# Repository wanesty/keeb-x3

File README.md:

# The RP2040 chip-powered V2 of this project has been relocated to [Codeberg](https://codeberg.org/Wanesty/keeb-x3)
it's developement will remain there for present and future iterations if I ultimately favor it over GitHub.

---

# keeb-x3
a 1800-style ortholinear keyboard with 105 keys

- this is my attempt as a contenporain keyboard, ditching the legacy staggered layout for ortho, which to me makes way more sense since we don't have to deal with typewriter hammers anymore.
- it is also made to be easily swapped between QWERTY, Dvorak and Colemak, to accentuate the need to detach ourselves from the 1873 typewriters.

#### The Pico's USB B have to be wired to the "keeb-x3"'s USB C port by using the "TP1, TP2, TP3" pads availlable on the bottom of the Pico

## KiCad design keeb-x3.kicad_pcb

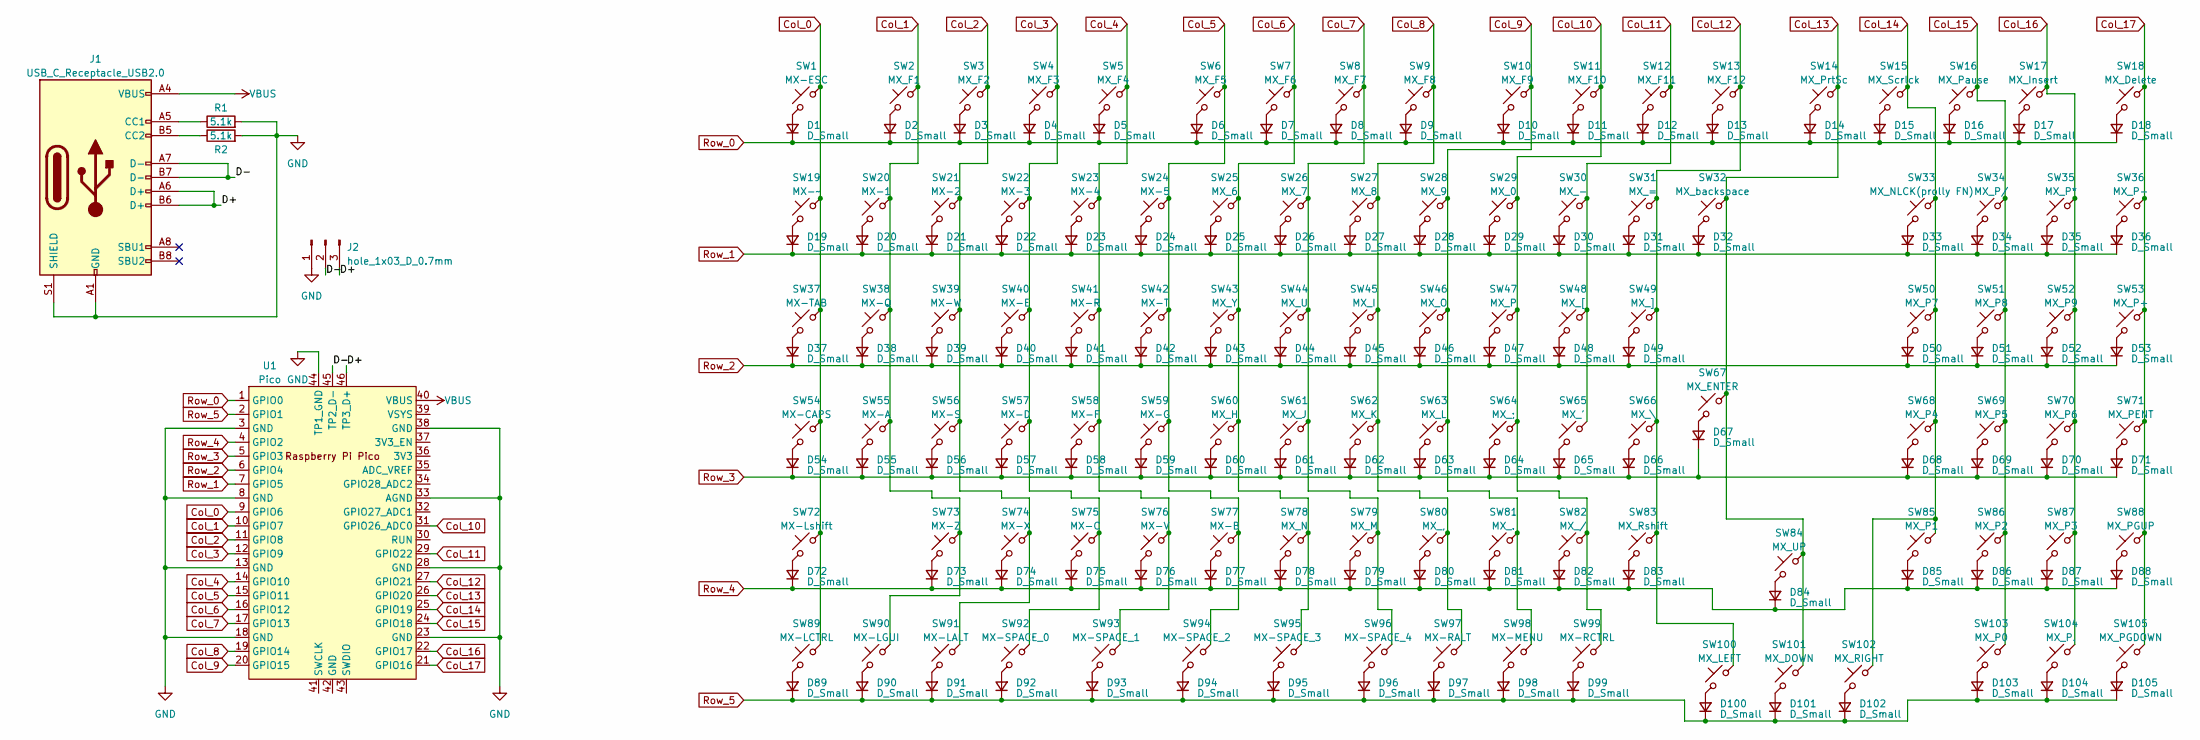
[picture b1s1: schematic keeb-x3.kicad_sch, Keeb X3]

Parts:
D1, D2, D3, D4, D5, D6, D7, D8, D9, D10, D11, D12, D13, D14, D15, D16, D17, D18, D19, D20, D21, D22, D23, D24, D25, D26, D27, D28, D29, D30, D31, D32, D33, D34, D35, D36, D37, D38, D39, D40, D41, D42, D43, D44, D45, D46, D47, D48, D49, D50, D51, D52, D53, D54, D55, D56, D57, D58, D59, D60, D61, D62, D63, D64, D65, D66, D67, D68, D69, D70, D71, D72, D73, D74, D75, D76, D77, D78, D79, D80, D81, D82, D83, D84, D85, D86, D87, D88, D89, D90, D91, D92, D93, D94, D95, D96, D97, D98, D99, D100, D101, D102, D103, D104, D105: D_Small; D_DO-35_SOD27_P7.62mm_Horizontal_ref_center
J1: USB_C_Receptacle_USB2.0; USB_C_Receptacle_GCT_USB4085
J2: hole_1x03_D_0.7mm
R1, R2: 5.1k; R_Axial_DIN0204_L3.6mm_D1.6mm_P7.62mm_Horizontal
SW1: MX-ESC; SW_Hotswap_Kailh_MX_plated_1.00u
SW2: MX_F1; SW_Hotswap_Kailh_MX_plated_1.00u
SW3: MX_F2; SW_Hotswap_Kailh_MX_plated_1.00u
SW4: MX_F3; SW_Hotswap_Kailh_MX_plated_1.00u
SW5: MX_F4; SW_Hotswap_Kailh_MX_plated_1.00u
SW6: MX_F5; SW_Hotswap_Kailh_MX_plated_1.00u
SW7: MX_F6; SW_Hotswap_Kailh_MX_plated_1.00u
SW8: MX_F7; SW_Hotswap_Kailh_MX_plated_1.00u
SW9: MX_F8; SW_Hotswap_Kailh_MX_plated_1.00u
SW10: MX_F9; SW_Hotswap_Kailh_MX_plated_1.00u
SW11: MX_F10; SW_Hotswap_Kailh_MX_plated_1.00u
SW12: MX_F11; SW_Hotswap_Kailh_MX_plated_1.00u
SW13: MX_F12; SW_Hotswap_Kailh_MX_plated_1.00u
SW14: MX_PrtSc; SW_Hotswap_Kailh_MX_plated_1.00u
SW15: MX_Scrlck; SW_Hotswap_Kailh_MX_plated_1.00u
SW16: MX_Pause; SW_Hotswap_Kailh_MX_plated_1.00u
SW17: MX_Insert; SW_Hotswap_Kailh_MX_plated_1.00u
SW18: MX_Delete; SW_Hotswap_Kailh_MX_plated_1.00u
SW19: MX-~; SW_Hotswap_Kailh_MX_plated_1.00u
SW20: MX-1; SW_Hotswap_Kailh_MX_plated_1.00u
SW21: MX-2; SW_Hotswap_Kailh_MX_plated_1.00u
SW22: MX-3; SW_Hotswap_Kailh_MX_plated_1.00u
SW23: MX-4; SW_Hotswap_Kailh_MX_plated_1.00u
SW24: MX-5; SW_Hotswap_Kailh_MX_plated_1.00u
SW25: MX_6; SW_Hotswap_Kailh_MX_plated_1.00u
SW26: MX_7; SW_Hotswap_Kailh_MX_plated_1.00u
SW27: MX_8; SW_Hotswap_Kailh_MX_plated_1.00u
SW28: MX_9; SW_Hotswap_Kailh_MX_plated_1.00u
SW29: MX_0; SW_Hotswap_Kailh_MX_plated_1.00u
SW30: MX_-; SW_Hotswap_Kailh_MX_plated_1.00u
SW31: MX_=; SW_Hotswap_Kailh_MX_plated_1.00u
SW32: MX_backspace; SW_Hotswap_Kailh_MX_plated_1.50u
SW33: MX_NLCK(prolly FN); SW_Hotswap_Kailh_MX_plated_1.00u
SW34: MX_P/; SW_Hotswap_Kailh_MX_plated_1.00u
SW35: MX_P*; SW_Hotswap_Kailh_MX_plated_1.00u
SW36: MX_P-; SW_Hotswap_Kailh_MX_plated_1.00u
SW37: MX-TAB; SW_Hotswap_Kailh_MX_plated_1.00u
SW38: MX-Q; SW_Hotswap_Kailh_MX_plated_1.00u
SW39: MX-W; SW_Hotswap_Kailh_MX_plated_1.00u
SW40: MX-E; SW_Hotswap_Kailh_MX_plated_1.00u
SW41: MX-R; SW_Hotswap_Kailh_MX_plated_1.00u
SW42: MX-T; SW_Hotswap_Kailh_MX_plated_1.00u
SW43: MX_Y; SW_Hotswap_Kailh_MX_plated_1.00u
SW44: MX_U; SW_Hotswap_Kailh_MX_plated_1.00u
SW45: MX_I; SW_Hotswap_Kailh_MX_plated_1.00u
SW46: MX_O; SW_Hotswap_Kailh_MX_plated_1.00u
SW47: MX_P; SW_Hotswap_Kailh_MX_plated_1.00u
SW48: MX_[; SW_Hotswap_Kailh_MX_plated_1.00u
SW49: MX_]; SW_Hotswap_Kailh_MX_plated_1.00u
SW50: MX_P7; SW_Hotswap_Kailh_MX_plated_1.00u
SW51: MX_P8; SW_Hotswap_Kailh_MX_plated_1.00u
SW52: MX_P9; SW_Hotswap_Kailh_MX_plated_1.00u
SW53: MX_P+; SW_Hotswap_Kailh_MX_plated_1.00u
SW54: MX-CAPS; SW_Hotswap_Kailh_MX_plated_1.00u
SW55: MX-A; SW_Hotswap_Kailh_MX_plated_1.00u
SW56: MX-S; SW_Hotswap_Kailh_MX_plated_1.00u
SW57: MX-D; SW_Hotswap_Kailh_MX_plated_1.00u
SW58: MX-F; SW_Hotswap_Kailh_MX_plated_1.00u
SW59: MX-G; SW_Hotswap_Kailh_MX_plated_1.00u
SW60: MX_H; SW_Hotswap_Kailh_MX_plated_1.00u
SW61: MX_J; SW_Hotswap_Kailh_MX_plated_1.00u
SW62: MX_K; SW_Hotswap_Kailh_MX_plated_1.00u
SW63: MX_L; SW_Hotswap_Kailh_MX_plated_1.00u
SW64: MX_;; SW_Hotswap_Kailh_MX_plated_1.00u
SW65: MX_'; SW_Hotswap_Kailh_MX_plated_1.00u
SW66: MX_\; SW_Hotswap_Kailh_MX_plated_1.00u
SW67: MX_ENTER; SW_Hotswap_Kailh_MX_plated_ISOEnter_180deg
SW68: MX_P4; SW_Hotswap_Kailh_MX_plated_1.00u
SW69: MX_P5; SW_Hotswap_Kailh_MX_plated_1.00u
SW70: MX_P6; SW_Hotswap_Kailh_MX_plated_1.00u
SW71: MX_PENT; SW_Hotswap_Kailh_MX_plated_1.00u
SW72: MX-Lshift; SW_Hotswap_Kailh_MX_plated_2.00u
SW73: MX-Z; SW_Hotswap_Kailh_MX_plated_1.00u
SW74: MX-X; SW_Hotswap_Kailh_MX_plated_1.00u
SW75: MX-C; SW_Hotswap_Kailh_MX_plated_1.00u
SW76: MX-V; SW_Hotswap_Kailh_MX_plated_1.00u
SW77: MX-B; SW_Hotswap_Kailh_MX_plated_1.00u
SW78: MX_N; SW_Hotswap_Kailh_MX_plated_1.00u
SW79: MX_M; SW_Hotswap_Kailh_MX_plated_1.00u
SW80: MX_,; SW_Hotswap_Kailh_MX_plated_1.00u
SW81: MX_.; SW_Hotswap_Kailh_MX_plated_1.00u
SW82: MX_/; SW_Hotswap_Kailh_MX_plated_1.00u
SW83: MX_Rshift; SW_Hotswap_Kailh_MX_plated_2.00u
SW84: MX_UP; SW_Hotswap_Kailh_MX_plated_1.00u
SW85: MX_P1; SW_Hotswap_Kailh_MX_plated_1.00u
SW86: MX_P2; SW_Hotswap_Kailh_MX_plated_1.00u
SW87: MX_P3; SW_Hotswap_Kailh_MX_plated_1.00u
SW88: MX_PGUP; SW_Hotswap_Kailh_MX_plated_1.00u
SW89: MX-LCTRL; SW_Hotswap_Kailh_MX_plated_1.00u
SW90: MX-LGUI; SW_Hotswap_Kailh_MX_plated_1.00u
SW91: MX-LALT; SW_Hotswap_Kailh_MX_plated_1.00u
SW92: MX-SPACE_0; SW_Hotswap_Kailh_MX_plated_1.00u
SW93: MX-SPACE_1; SW_Hotswap_Kailh_MX_plated_2.00u
SW94: MX-SPACE_2; SW_Hotswap_Kailh_MX_plated_1.00u
SW95: MX-SPACE_3; SW_Hotswap_Kailh_MX_plated_2.00u
SW96: MX-SPACE_4; SW_Hotswap_Kailh_MX_plated_1.00u
SW97: MX-RALT; SW_Hotswap_Kailh_MX_plated_1.00u
SW98: MX-MENU; SW_Hotswap_Kailh_MX_plated_1.00u
SW99: MX-RCTRL; SW_Hotswap_Kailh_MX_plated_1.00u
SW100: MX_LEFT; SW_Hotswap_Kailh_MX_plated_1.00u
SW101: MX_DOWN; SW_Hotswap_Kailh_MX_plated_1.00u
SW102: MX_RIGHT; SW_Hotswap_Kailh_MX_plated_1.00u
SW103: MX_P0; SW_Hotswap_Kailh_MX_plated_1.00u
SW104: MX_P.; SW_Hotswap_Kailh_MX_plated_1.00u
SW105: MX_PGDOWN; SW_Hotswap_Kailh_MX_plated_1.00u
U1: Pico; RPi_Pico_SMD_TH

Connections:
/D+: J1.A6 (D+), J1.B6 (D+), J2.3, U1.46 (TP3_D+)
/D-: J1.A7 (D-), J1.B7 (D-), J2.2, U1.45 (TP2_D-)
Col_0: SW1.1, SW19.1, SW37.1, SW54.1, SW72.1, SW89.1, U1.9 (GPIO6)
Col_1: SW2.1, SW20.1, SW38.1, SW55.1, SW73.1, SW90.1, U1.10 (GPIO7)
Col_2: SW3.1, SW21.1, SW39.1, SW56.1, SW74.1, SW91.1, U1.11 (GPIO8)
Col_3: SW4.1, SW22.1, SW40.1, SW57.1, SW75.1, SW92.1, U1.12 (GPIO9)
Col_4: SW5.1, SW23.1, SW41.1, SW58.1, SW76.1, SW93.1, U1.14 (GPIO10)
Col_5: SW6.1, SW24.1, SW42.1, SW59.1, SW77.1, SW94.1, U1.15 (GPIO11)
Col_6: SW7.1, SW25.1, SW43.1, SW60.1, SW78.1, SW95.1, U1.16 (GPIO12)
Col_7: SW8.1, SW26.1, SW44.1, SW61.1, SW79.1, SW96.1, U1.17 (GPIO13)
Col_8: SW9.1, SW27.1, SW45.1, SW62.1, SW80.1, SW97.1, U1.19 (GPIO14)
Col_9: SW10.1, SW28.1, SW46.1, SW63.1, SW81.1, SW98.1, U1.20 (GPIO15)
Col_10: SW11.1, SW29.1, SW47.1, SW64.1, SW82.1, SW99.1, U1.31 (GPIO26_ADC0)
Col_11: SW12.1, SW30.1, SW48.1, SW65.1, U1.29 (GPIO22)
Col_12: SW13.1, SW31.1, SW49.1, SW66.1, SW83.1, SW100.1, U1.27 (GPIO21)
Col_13: SW14.1, SW32.1, SW67.1, SW84.1, SW101.1, U1.26 (GPIO20)
Col_14: SW15.1, SW33.1, SW50.1, SW68.1, SW85.1, SW102.1, U1.25 (GPIO19)
Col_15: SW16.1, SW34.1, SW51.1, SW69.1, SW86.1, SW103.1, U1.24 (GPIO18)
Col_16: SW17.1, SW35.1, SW52.1, SW70.1, SW87.1, SW104.1, U1.22 (GPIO17)
Col_17: SW18.1, SW36.1, SW53.1, SW71.1, SW88.1, SW105.1, U1.21 (GPIO16)
GND: J1.A1 (GND), J1.A12 (GND), J1.B1 (GND), J1.B12 (GND), J1.S1 (SHIELD), J2.1, R1.2, R2.2, U1.3 (GND), U1.8 (GND), U1.13 (GND), U1.18 (GND), U1.23 (GND), U1.28 (GND), U1.33 (AGND), U1.38 (GND), U1.44 (TP1_GND)
unnamed: D1.2 (A), SW1.2
unnamed: D2.2 (A), SW2.2
unnamed: D3.2 (A), SW3.2
unnamed: D4.2 (A), SW4.2
unnamed: D5.2 (A), SW5.2
unnamed: D6.2 (A), SW6.2
unnamed: D7.2 (A), SW7.2
unnamed: D8.2 (A), SW8.2
unnamed: D9.2 (A), SW9.2
unnamed: D10.2 (A), SW10.2
unnamed: D11.2 (A), SW11.2
unnamed: D12.2 (A), SW12.2
unnamed: D13.2 (A), SW13.2
unnamed: D14.2 (A), SW14.2
unnamed: D15.2 (A), SW15.2
unnamed: D16.2 (A), SW16.2
unnamed: D17.2 (A), SW17.2
unnamed: D18.2 (A), SW18.2
unnamed: D19.2 (A), SW19.2
unnamed: D20.2 (A), SW20.2
unnamed: D21.2 (A), SW21.2
unnamed: D22.2 (A), SW22.2
unnamed: D23.2 (A), SW23.2
unnamed: D24.2 (A), SW24.2
unnamed: D25.2 (A), SW25.2
unnamed: D26.2 (A), SW26.2
unnamed: D27.2 (A), SW27.2
unnamed: D28.2 (A), SW28.2
unnamed: D29.2 (A), SW29.2
unnamed: D30.2 (A), SW30.2
unnamed: D31.2 (A), SW31.2
unnamed: D32.2 (A), SW32.2
unnamed: D33.2 (A), SW33.2
unnamed: D34.2 (A), SW34.2
unnamed: D35.2 (A), SW35.2
unnamed: D36.2 (A), SW36.2
unnamed: D37.2 (A), SW37.2
unnamed: D38.2 (A), SW38.2
unnamed: D39.2 (A), SW39.2
unnamed: D40.2 (A), SW40.2
unnamed: D41.2 (A), SW41.2
unnamed: D42.2 (A), SW42.2
unnamed: D43.2 (A), SW43.2
unnamed: D44.2 (A), SW44.2
unnamed: D45.2 (A), SW45.2
unnamed: D46.2 (A), SW46.2
unnamed: D47.2 (A), SW47.2
unnamed: D48.2 (A), SW48.2
unnamed: D49.2 (A), SW49.2
unnamed: D50.2 (A), SW50.2
unnamed: D51.2 (A), SW51.2
unnamed: D52.2 (A), SW52.2
unnamed: D53.2 (A), SW53.2
unnamed: D54.2 (A), SW54.2
unnamed: D55.2 (A), SW55.2
unnamed: D56.2 (A), SW56.2
unnamed: D57.2 (A), SW57.2
unnamed: D58.2 (A), SW58.2
unnamed: D59.2 (A), SW59.2
unnamed: D60.2 (A), SW60.2
unnamed: D61.2 (A), SW61.2
unnamed: D62.2 (A), SW62.2
unnamed: D63.2 (A), SW63.2
unnamed: D64.2 (A), SW64.2
unnamed: D65.2 (A), SW65.2
unnamed: D66.2 (A), SW66.2
unnamed: D67.2 (A), SW67.2
unnamed: D68.2 (A), SW68.2
unnamed: D69.2 (A), SW69.2
unnamed: D70.2 (A), SW70.2
unnamed: D71.2 (A), SW71.2
unnamed: D72.2 (A), SW72.2
unnamed: D73.2 (A), SW73.2
unnamed: D74.2 (A), SW74.2
unnamed: D75.2 (A), SW75.2
unnamed: D76.2 (A), SW76.2
unnamed: D77.2 (A), SW77.2
unnamed: D78.2 (A), SW78.2
unnamed: D79.2 (A), SW79.2
unnamed: D80.2 (A), SW80.2
unnamed: D81.2 (A), SW81.2
unnamed: D82.2 (A), SW82.2
unnamed: D83.2 (A), SW83.2
unnamed: D84.2 (A), SW84.2
unnamed: D85.2 (A), SW85.2
unnamed: D86.2 (A), SW86.2
unnamed: D87.2 (A), SW87.2
unnamed: D88.2 (A), SW88.2
unnamed: D89.2 (A), SW89.2
unnamed: D90.2 (A), SW90.2
unnamed: D91.2 (A), SW91.2
unnamed: D92.2 (A), SW92.2
unnamed: D93.2 (A), SW93.2
unnamed: D94.2 (A), SW94.2
unnamed: D95.2 (A), SW95.2
unnamed: D96.2 (A), SW96.2
unnamed: D97.2 (A), SW97.2
unnamed: D98.2 (A), SW98.2
unnamed: D99.2 (A), SW99.2
unnamed: D100.2 (A), SW100.2
unnamed: D101.2 (A), SW101.2
unnamed: D102.2 (A), SW102.2
unnamed: D103.2 (A), SW103.2
unnamed: D104.2 (A), SW104.2
unnamed: D105.2 (A), SW105.2
unnamed: J1.A5 (CC1), R1.1
unnamed: J1.B5 (CC2), R2.1
Row_0: D1.1 (K), D2.1 (K), D3.1 (K), D4.1 (K), D5.1 (K), D6.1 (K), D7.1 (K), D8.1 (K), D9.1 (K), D10.1 (K), D11.1 (K), D12.1 (K), D13.1 (K), D14.1 (K), D15.1 (K), D16.1 (K), D17.1 (K), D18.1 (K), U1.1 (GPIO0)
Row_1: D19.1 (K), D20.1 (K), D21.1 (K), D22.1 (K), D23.1 (K), D24.1 (K), D25.1 (K), D26.1 (K), D27.1 (K), D28.1 (K), D29.1 (K), D30.1 (K), D31.1 (K), D32.1 (K), D33.1 (K), D34.1 (K), D35.1 (K), D36.1 (K), U1.7 (GPIO5)
Row_2: D37.1 (K), D38.1 (K), D39.1 (K), D40.1 (K), D41.1 (K), D42.1 (K), D43.1 (K), D44.1 (K), D45.1 (K), D46.1 (K), D47.1 (K), D48.1 (K), D49.1 (K), D50.1 (K), D51.1 (K), D52.1 (K), D53.1 (K), U1.6 (GPIO4)
Row_3: D54.1 (K), D55.1 (K), D56.1 (K), D57.1 (K), D58.1 (K), D59.1 (K), D60.1 (K), D61.1 (K), D62.1 (K), D63.1 (K), D64.1 (K), D65.1 (K), D66.1 (K), D67.1 (K), D68.1 (K), D69.1 (K), D70.1 (K), D71.1 (K), U1.5 (GPIO3)
Row_4: D72.1 (K), D73.1 (K), D74.1 (K), D75.1 (K), D76.1 (K), D77.1 (K), D78.1 (K), D79.1 (K), D80.1 (K), D81.1 (K), D82.1 (K), D83.1 (K), D84.1 (K), D85.1 (K), D86.1 (K), D87.1 (K), D88.1 (K), U1.4 (GPIO2)
Row_5: D89.1 (K), D90.1 (K), D91.1 (K), D92.1 (K), D93.1 (K), D94.1 (K), D95.1 (K), D96.1 (K), D97.1 (K), D98.1 (K), D99.1 (K), D100.1 (K), D101.1 (K), D102.1 (K), D103.1 (K), D104.1 (K), D105.1 (K), U1.2 (GPIO1)
VBUS: J1.A4 (VBUS), J1.A9 (VBUS), J1.B4 (VBUS), J1.B9 (VBUS), U1.40 (VBUS)

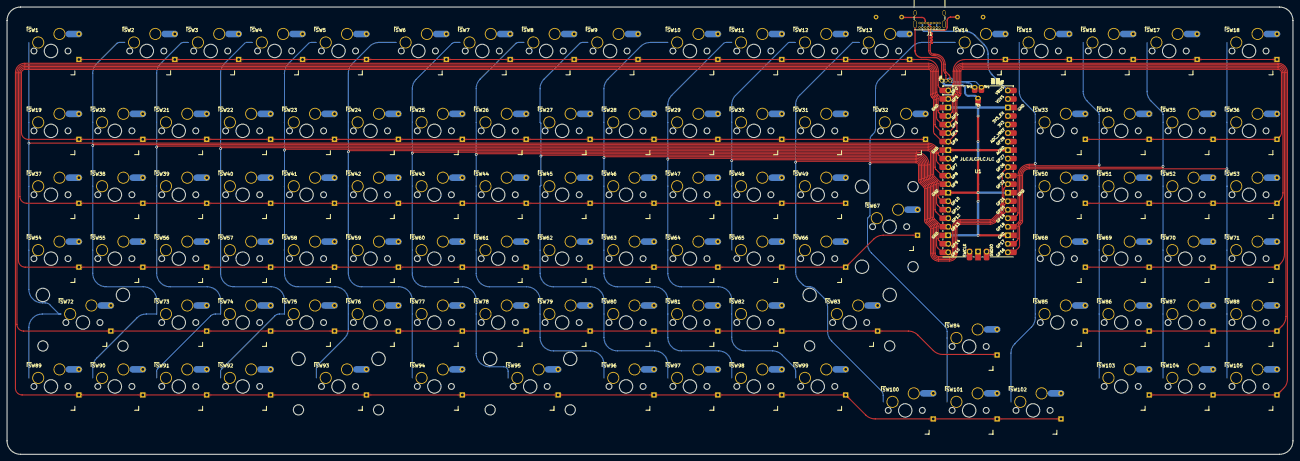
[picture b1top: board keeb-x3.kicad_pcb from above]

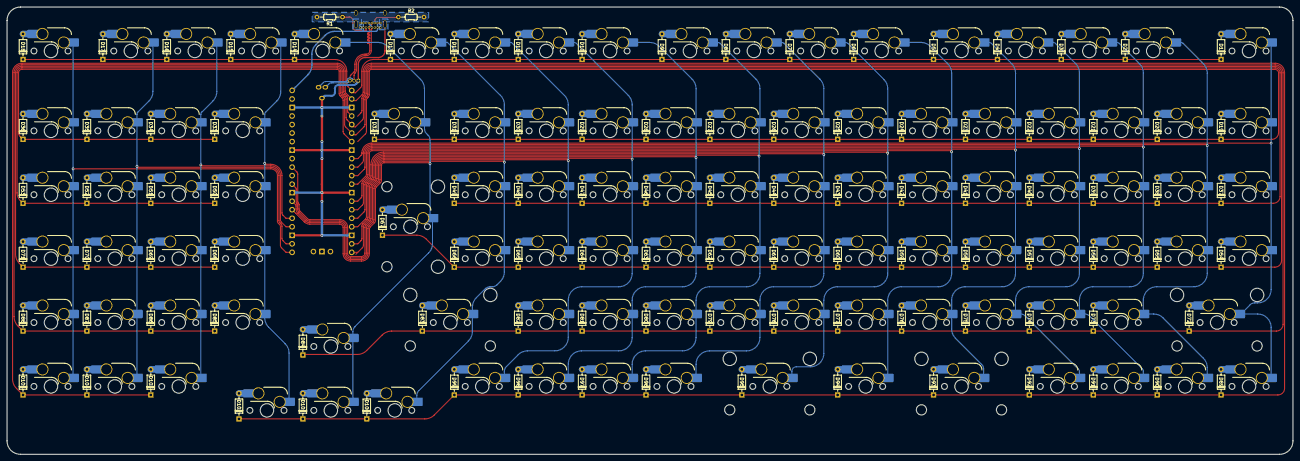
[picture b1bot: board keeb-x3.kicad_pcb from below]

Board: 2 copper layers, 383.4 x 133.3 mm, 220 parts (107 on the bottom side), 135 nets.

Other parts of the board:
stab_Lshift: Stabilizer_Cherry_MX_2.00u
stab_Rshift: Stabilizer_Cherry_MX_2.00u
stab_Shift1: Stabilizer_Cherry_MX_2.00u
stab_Space2: Stabilizer_Cherry_MX_2.00u
stab_enter: Stabilizer_Cherry_MX_2.00u

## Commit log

2023-04-29 licensefile
2023-04-29 pics and readmeS
2023-04-29 switch to MIT to add warranty disclaimer
2023-04-29 got rid of teardrops on pico to fix clearance issues
2023-04-29 pcb renders
2023-04-30 last(maybe) pcb revision before attempting a V2 branch
2023-04-30 cleanup
2023-04-30 .gitignore
2023-04-30 pcb rev & gitignore
2023-05-05 archive.md
